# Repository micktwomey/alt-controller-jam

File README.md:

# CTRL.ALT GameCraft 2023

Repo holding the hardware and code behind the controller components used in https://www.gamecraft.it/events/altctrljam-2023/

# Hardware

A [Raspberry Pi Pico](https://www.raspberrypi.com/products/raspberry-pi-pico/) running [CircuitPython](https://circuitpython.org/board/raspberry_pi_pico/) acts as a HID keyboard device.

Two (or more) button pads are connected to the Pico using jumper cables. Each button pad has 4 buttons.

You can position these anywhere you want on an alternative controller. Embed them in cardboard, stick onto things, etc.

[KiCad](https://www.kicad.org/) is used to design the boards. You can even see me following the tutorial in [kicad-tutorial](./kikad-tutorial/)!

[JLCPCB](https://jlcpcb.com/) was used to print the boards. Elbow grease and lots of solder was used to assemble the boards.

The schematics can be found in [dpad](./dpad/).

# Software

The Pico runs [CircuitPython](https://circuitpython.org/) and uses Adafruit's HID library to emulate a keyboard. It's also possible to emulate a mouse and a gamepad (there are some experiments for gamepad emulation in [experiments](./src/gamecraft_alt_controller_jam_board/experiments/)).

Code execution order:

1. [boot.py](./boards/circuitpython/boot.py) is run *once* on board startup to configure it. Here we enable keyboard emulation. If you change this you need to unplug and plug the board back in. If you want to pretend to be a mouse or gamepad this is where you do it.
2. Next [code.py](./boards/circuitpython/code.py) is run to configure the button mapping and listen for events. Editing this should immediately restart the code and use your changes. If you need to change the button mappings this is where you do it.

When running the library code lives in `lib` on the pico but lives in [src](./src/) here in GitHub.

- [gamecraft_alt_controller_jam_board.configurations](./src/gamecraft_alt_controller_jam_board/configurations.py) contains different example keyboard mappings you can use.
- [gamecraft_alt_controller_jam_board.hardware](./src/gamecraft_alt_controller_jam_board/hardware.py) contains mappings for pins.
- [gamecraft_alt_controller_jam_board.keyboard](./src/gamecraft_alt_controller_jam_board/keyboard.py) contains the code which acts as a keyboard, responding to GPIO pins (button clicks) and sending out keycodes.

# Building and Deploying to a Pico

[just](https://just.systems/) is used to run the build and deployment steps.

[poetry](https://python-poetry.org/) is used to manage local tool dependencies. It's also used to install libraries into your development environment, but these won't allow you to run the code on your desktop. They're primarily intended to allow for error checking.

Note that the default paths in the [justfile](./justfile) are Apple Mac defaults, you'll need to adjust them for your machine.

1. To install dependencies: `poetry install`
2. To build: `just build`
3. To flash CircuitPython onto a Pico:
    1. Hold down the `bootsel` button on the Pico while plugging in the USB cable into your machine
    2. Keep holding it down until a `RPI-RP2` disk is mounted
    3. Run `just install-firmware`
4. To deploy the built code onto the pico: `just deploy`

You can make this process a little more efficient using:

1. Run `just watch` to see which disk is mounted
2. After plugging in the pico use `just install-firmware && just deploy && just eject` in another terminal to flash the firmware and install the code in one step.

## Setting Up

If you're using [mise](https://mise.jdx.dev/) it should activate automatically.

Otherwise you need [uv](https://docs.astral.sh/uv/) and [just](https://just.systems/) installed.

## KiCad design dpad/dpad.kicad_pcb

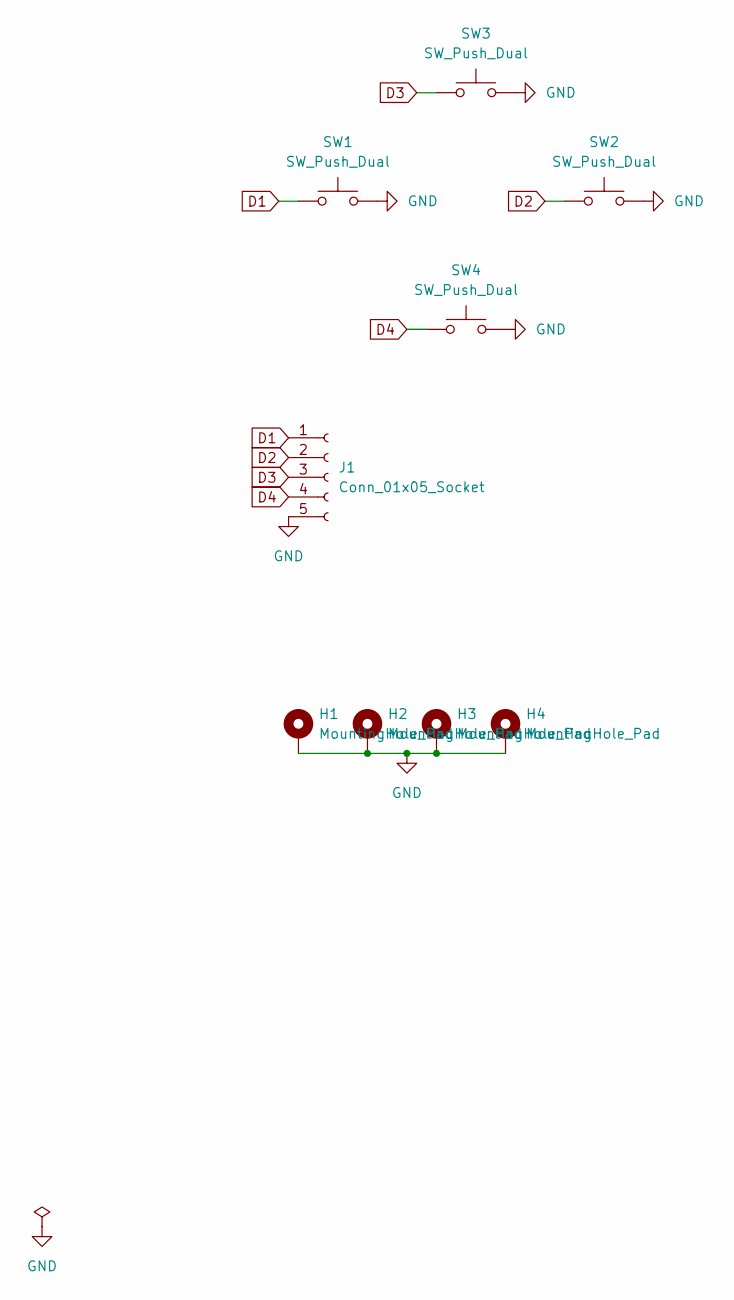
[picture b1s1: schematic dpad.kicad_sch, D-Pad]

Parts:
H1, H2, H3, H4: MountingHole_Pad; MountingHole_2.2mm_M2_Pad
J1: Conn_01x05_Socket; PinHeader_1x05_P2.54mm_Vertical
SW1, SW2, SW3, SW4: SW_Push_Dual; SW_PUSH_6mm

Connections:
D1: J1.1, SW1.1
D2: J1.2, SW2.1
D3: J1.3, SW3.1
D4: J1.4, SW4.1
GND: H1.1, H2.1, H3.1, H4.1, J1.5, SW1.2, SW2.2, SW3.2, SW4.2

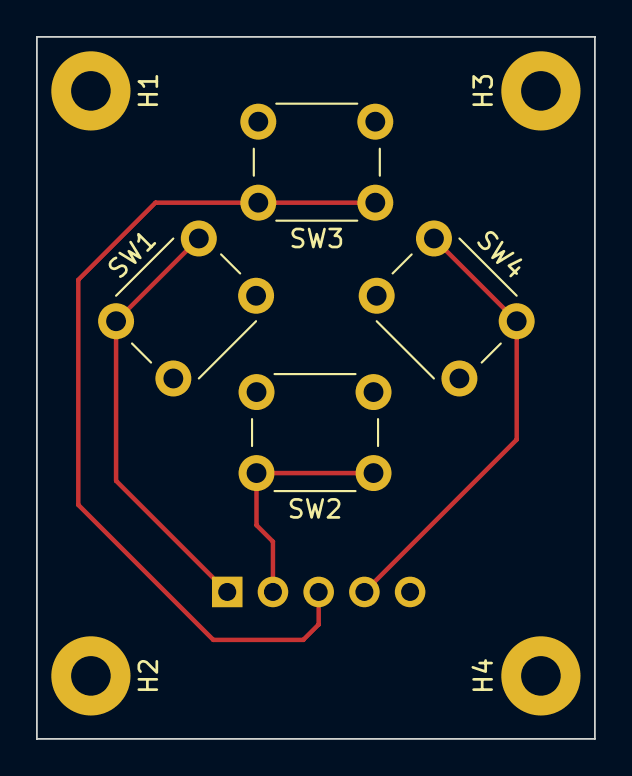
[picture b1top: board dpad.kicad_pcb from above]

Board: 2 copper layers, 31.0 x 39.0 mm, 9 parts (1 on the bottom side), 5 nets.

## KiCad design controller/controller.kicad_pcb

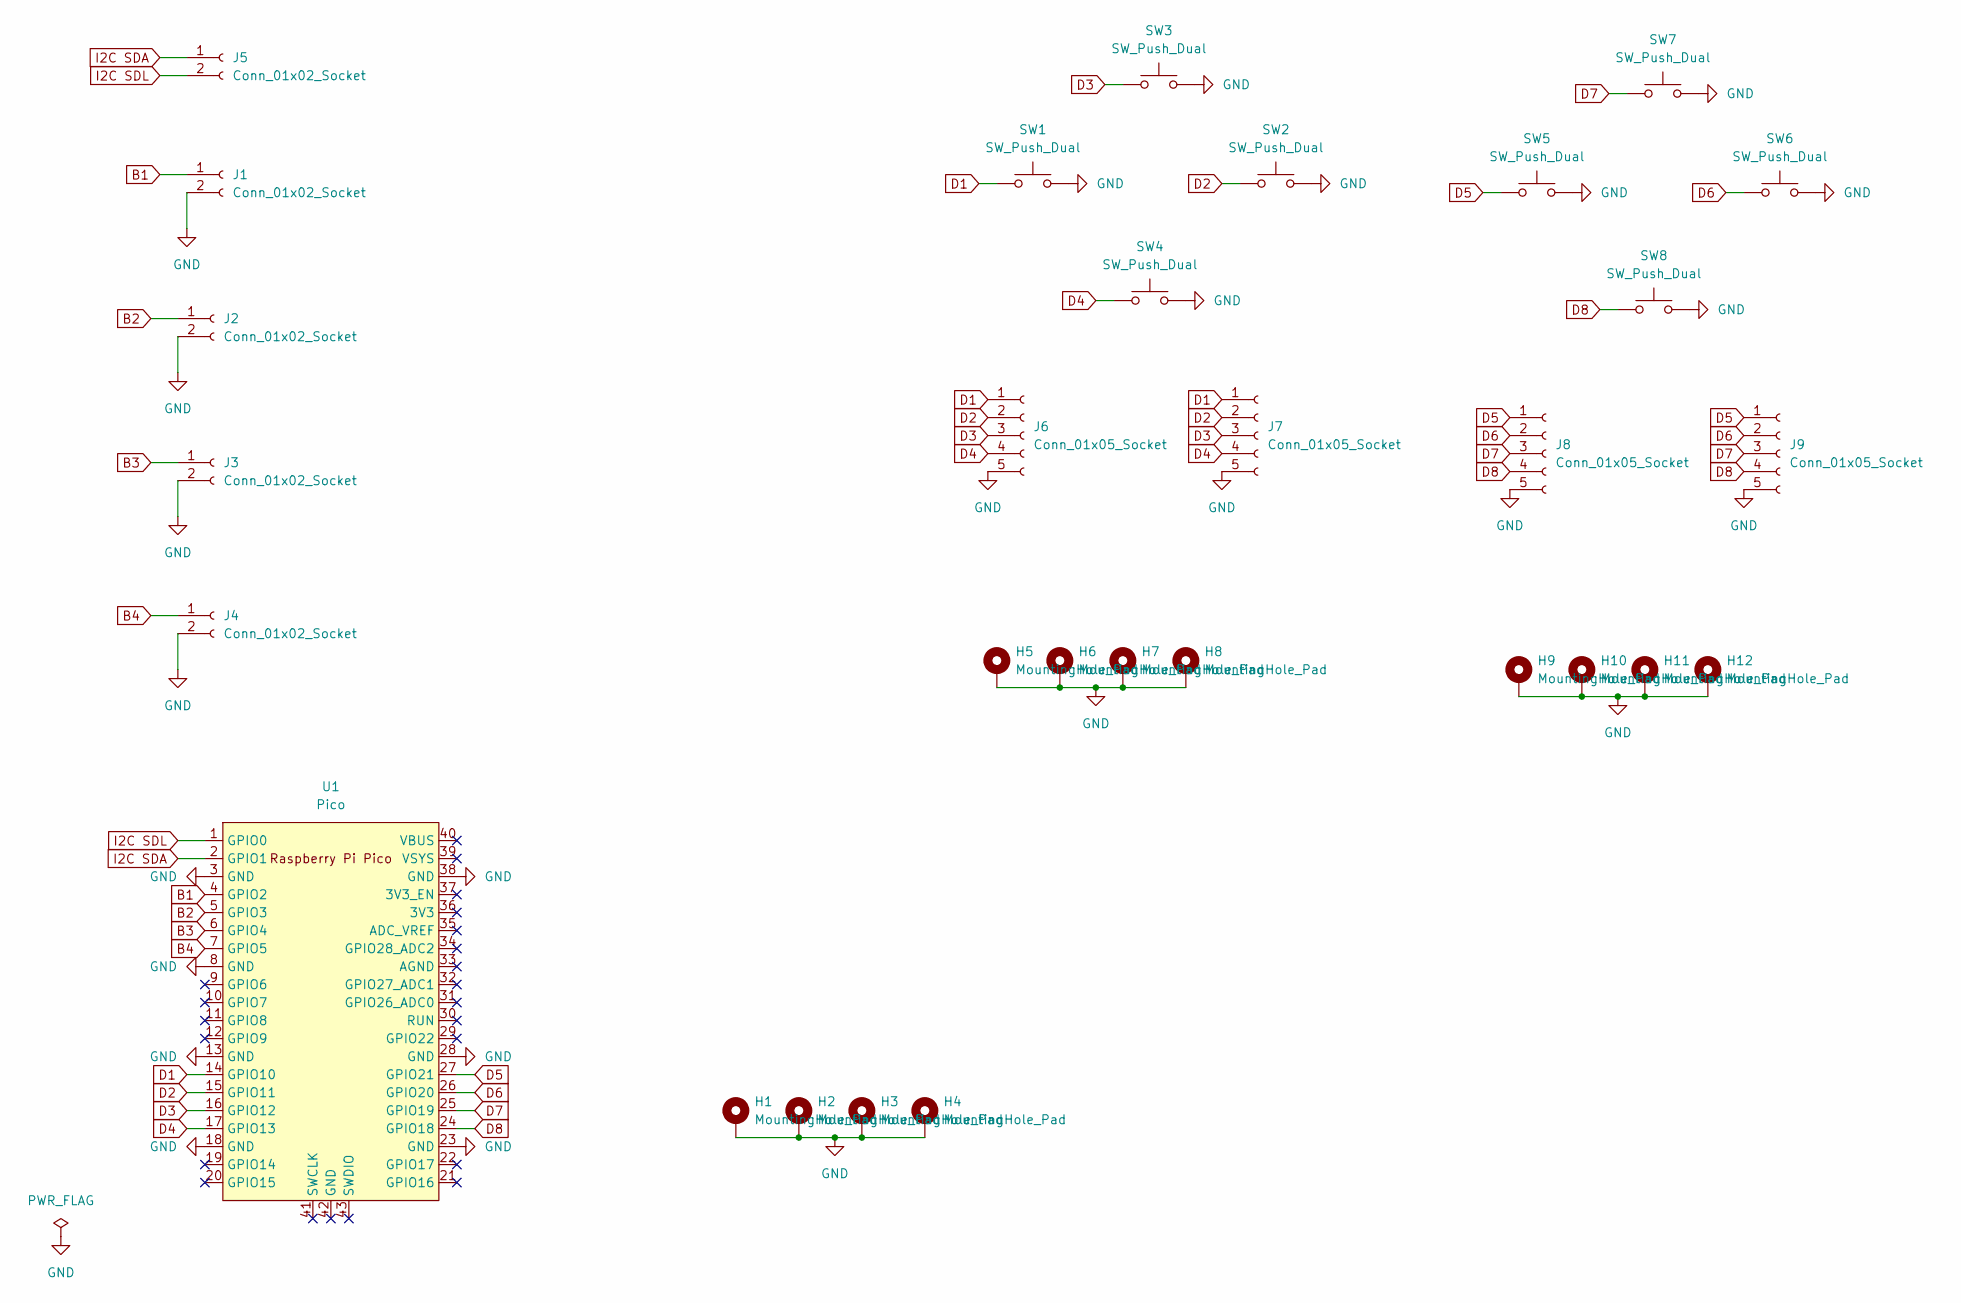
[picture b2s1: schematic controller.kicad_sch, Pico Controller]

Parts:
H1, H2, H3, H4, H5, H6, H7, H8, H9, H10, H11, H12: MountingHole_Pad; MountingHole_3.2mm_M3_Pad
J1, J2, J3, J4, J5: Conn_01x02_Socket; JST_XH_B2B-XH-AM_1x02_P2.50mm_Vertical
J6, J7, J8, J9: Conn_01x05_Socket; PinHeader_1x05_P1.00mm_Vertical
SW1, SW2, SW3, SW4, SW5, SW6, SW7, SW8: SW_Push_Dual; SW_PUSH-12mm
U1: Pico; RPi_Pico_SMD_TH

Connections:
B1: J1.1, U1.4 (GPIO2)
B2: J2.1, U1.5 (GPIO3)
B3: J3.1, U1.6 (GPIO4)
B4: J4.1, U1.7 (GPIO5)
D1: J6.1, J7.1, SW1.1, U1.14 (GPIO10)
D2: J6.2, J7.2, SW2.1, U1.15 (GPIO11)
D3: J6.3, J7.3, SW3.1, U1.16 (GPIO12)
D4: J6.4, J7.4, SW4.1, U1.17 (GPIO13)
D5: J8.1, J9.1, SW5.1, U1.27 (GPIO21)
D6: J8.2, J9.2, SW6.1, U1.26 (GPIO20)
D7: J8.3, J9.3, SW7.1, U1.25 (GPIO19)
D8: J8.4, J9.4, SW8.1, U1.24 (GPIO18)
GND: H1.1, H2.1, H3.1, H4.1, H5.1, H6.1, H7.1, H8.1, H9.1, H10.1, H11.1, H12.1, J1.2, J2.2, J3.2, J4.2, J6.5, J7.5, J8.5, J9.5, SW1.2, SW2.2, SW3.2, SW4.2, SW5.2, SW6.2, SW7.2, SW8.2, U1.3 (GND), U1.8 (GND), U1.13 (GND), U1.18 (GND), U1.23 (GND), U1.28 (GND), U1.38 (GND)
I2C SDA: J5.1, U1.2 (GPIO1)
I2C SDL: J5.2, U1.1 (GPIO0)

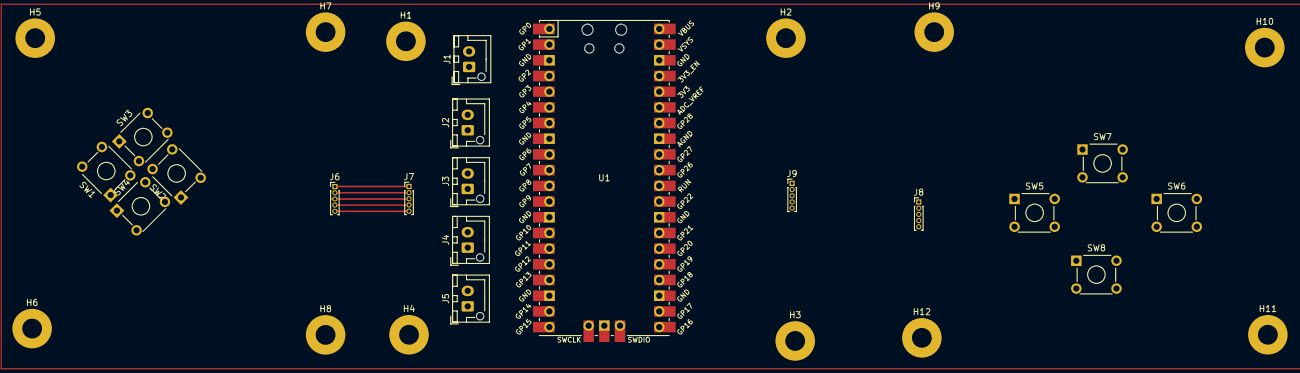
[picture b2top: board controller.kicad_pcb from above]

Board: 2 copper layers, 30 parts (0 on the bottom side), 15 nets.

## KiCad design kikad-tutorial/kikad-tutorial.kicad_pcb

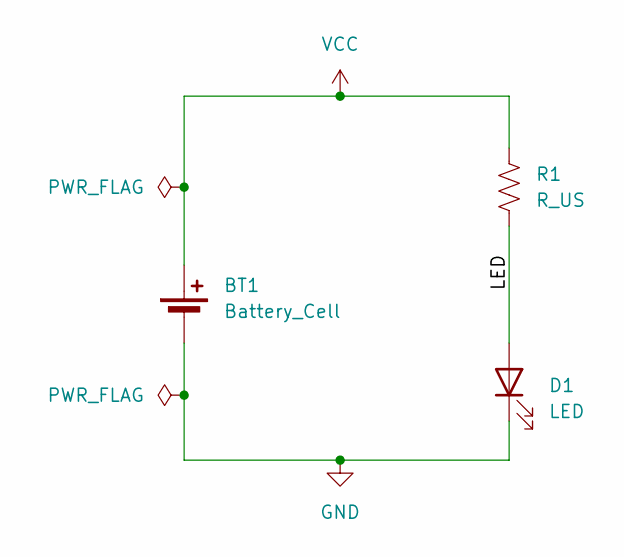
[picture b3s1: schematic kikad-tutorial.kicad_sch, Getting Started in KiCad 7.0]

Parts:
BT1: Battery_Cell; BatteryHolder_Keystone_1058_1x2032
D1: LED; LED_D5.0mm
R1: R_US; R_Axial_DIN0309_L9.0mm_D3.2mm_P12.70mm_Horizontal

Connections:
/LED: D1.2 (A), R1.2
GND: BT1.2 (-), D1.1 (K)
VCC: BT1.1 (+), R1.1

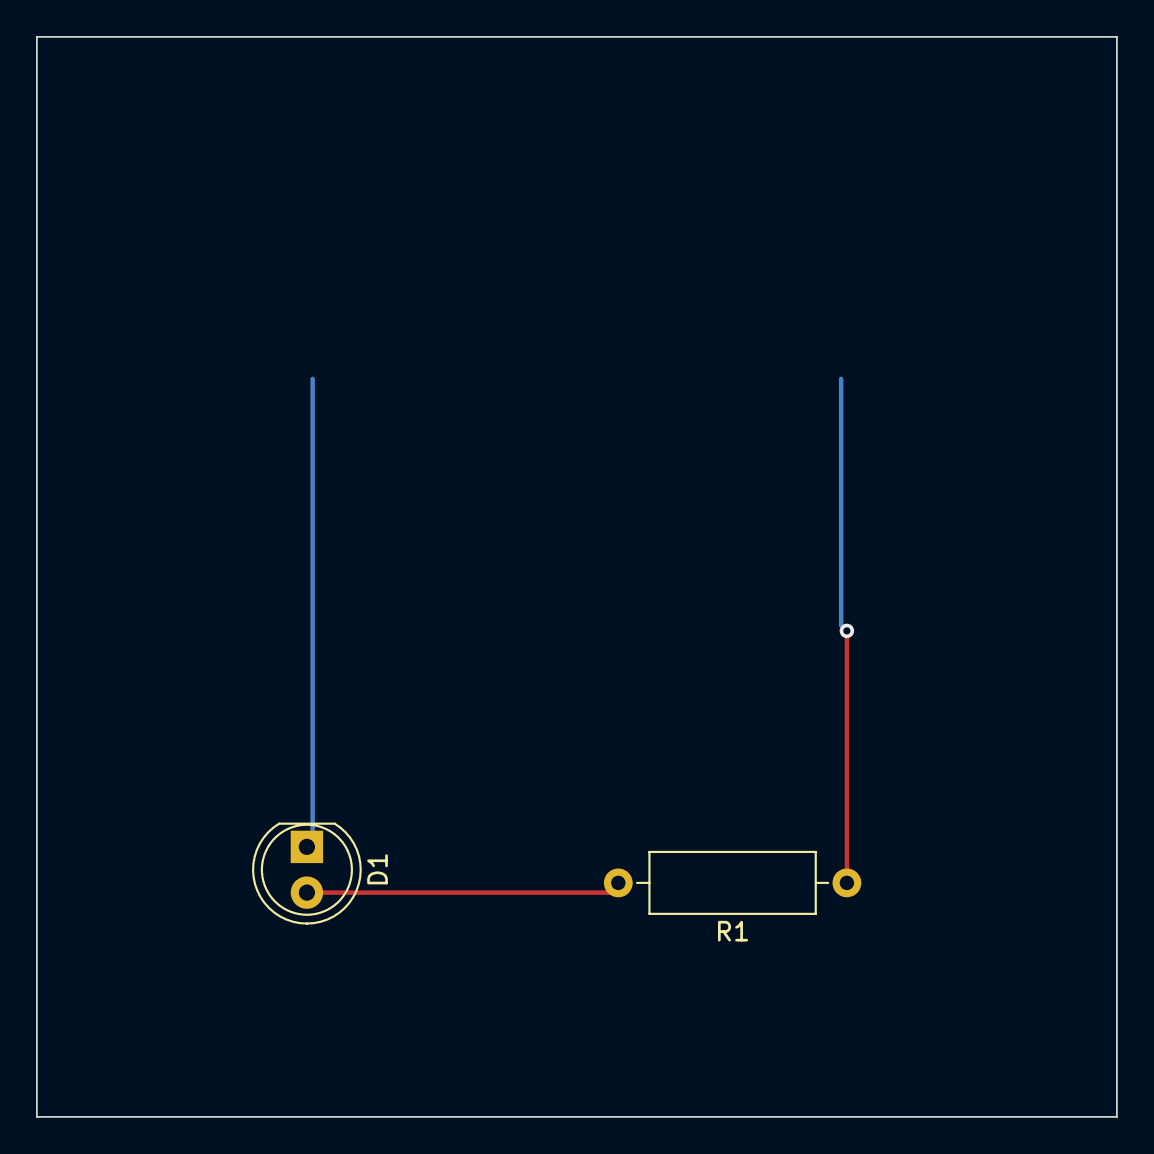
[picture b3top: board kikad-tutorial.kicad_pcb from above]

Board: 2 copper layers, 60.0 x 60.0 mm, 3 parts (1 on the bottom side), 3 nets.

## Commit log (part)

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2023-09-21 WIP: starting on controller
2023-09-25 Splitting dpad out into its own board
2023-09-25 Removing files which don't need to be committed
2023-09-26 dpad v0
2023-10-29 dpad v1
2023-10-30 Initial HID controller using circuitpython
    Using circuitpython to act as a HID keyboard.
    Also explored acting as a gamepad but this likely requires more configuration to map buttons.
2023-10-30 Create keyboard input controller and sample configurations
    Should be easy enough to customize or switch configurations.
    Focussing on keyboard only for now.
2023-10-30 Add just install-circuitpython action to download and install circuitpython
2023-10-30 Experimental build task
    Commented out for now.
2023-11-01 Add more actions to justfile
    Can now flash firmware, copy code and eject in one: `just install-firmware && just deploy && just eject`
    Add `just watch` so you can see the state of the connected device
2023-11-02 Use smaller image
2023-11-02 Add note on setting up
2024-03-20 Bump black from 23.10.1 to 24.3.0
    Bumps [black](https://github.com/psf/black) from 23.10.1 to 24.3.0.
    - [Release notes](https://github.com/psf/black/releases)
    - [Changelog](https://github.com/psf/black/blob/main/CHANGES.md)
    - [Commits](https://github.com/psf/black/compare/23.10.1...24.3.0)
    ---
    updated-dependencies:
2024-04-12 Bump idna from 3.4 to 3.7
    Bumps [idna](https://github.com/kjd/idna) from 3.4 to 3.7.
    - [Release notes](https://github.com/kjd/idna/releases)
    - [Changelog](https://github.com/kjd/idna/blob/master/HISTORY.rst)
    - [Commits](https://github.com/kjd/idna/compare/v3.4...v3.7)
    ---
    updated-dependencies:
2024-05-21 --- updated-dependencies: - dependency-name: requests dependency-type: indirect ...
2024-06-12 Creating initial case in Tinkercad
2024-06-12 Bump requests from 2.31.0 to 2.32.2
    Bumps [requests](https://github.com/psf/requests) from 2.31.0 to 2.32.2.
    - [Release notes](https://github.com/psf/requests/releases)
    - [Changelog](https://github.com/psf/requests/blob/main/HISTORY.md)
    - [Commits](https://github.com/psf/requests/compare/v2.31.0...v2.32.2)
    ---
    updated-dependencies:
2024-06-13 Next version of case
2024-06-13 Minor tweak to case
2024-06-14 Bump dependencies
2024-06-14 Add a 20x 3D print job
2024-06-14 Add fab outputs
2024-06-14 Moved configuration into code.py, much easier to read
    Tidied up dependencies a bit
2024-06-17 Bump urllib3 from 2.2.1 to 2.2.2
    Bumps [urllib3](https://github.com/urllib3/urllib3) from 2.2.1 to 2.2.2.
    - [Release notes](https://github.com/urllib3/urllib3/releases)
    - [Changelog](https://github.com/urllib3/urllib3/blob/main/CHANGES.rst)
    - [Commits](https://github.com/urllib3/urllib3/compare/2.2.1...2.2.2)
    ---
    updated-dependencies:
